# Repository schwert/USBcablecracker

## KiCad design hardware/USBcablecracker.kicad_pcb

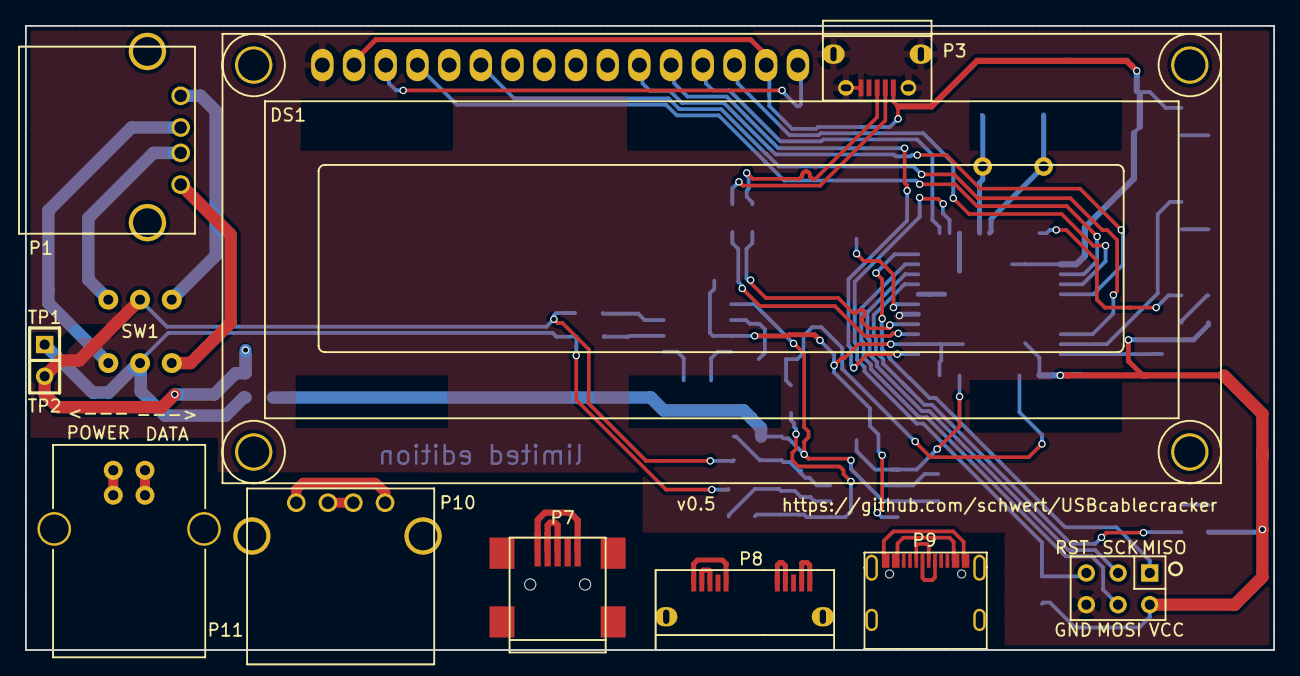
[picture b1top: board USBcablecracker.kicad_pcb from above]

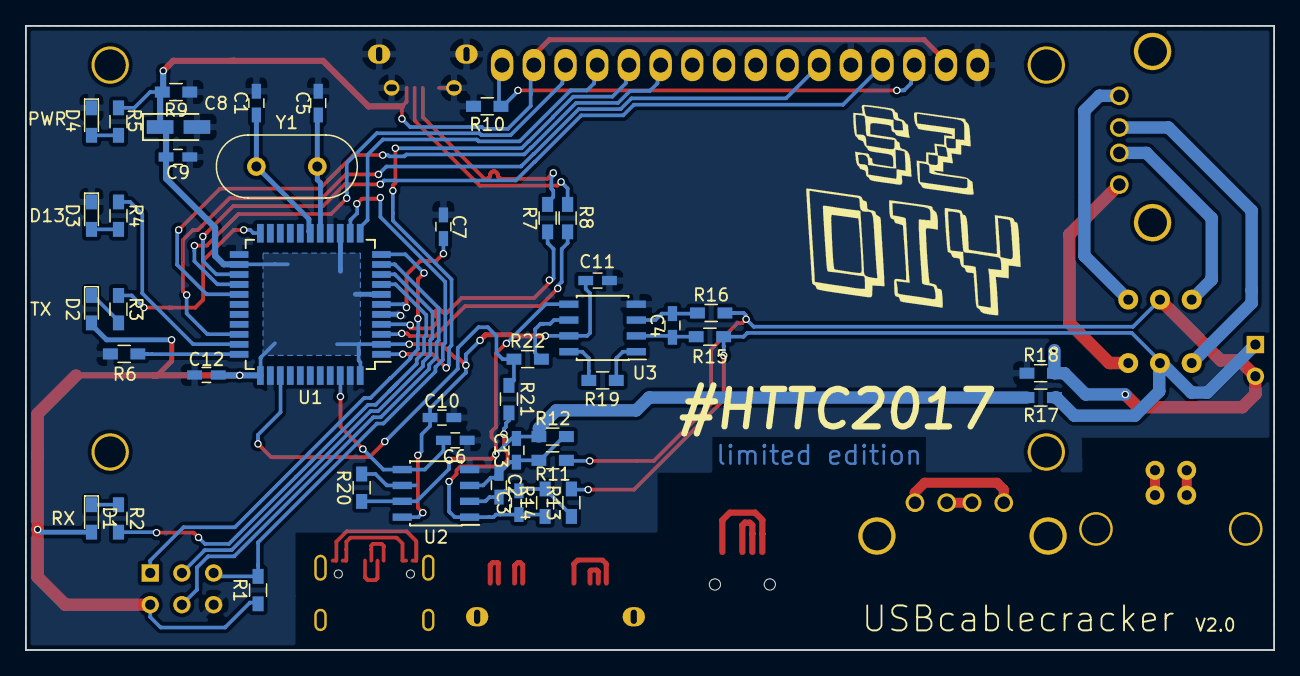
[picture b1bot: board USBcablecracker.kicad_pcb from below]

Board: 2 copper layers, 100.0 x 50.0 mm, 54 parts (43 on the bottom side), 60 nets.

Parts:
C1, C5: 15P; C_0603_HandSoldering
C2, C3, C4, C13: 1nF; C_0603_HandSoldering
C6, C9, C10, C11, C12: 100nF; C_0603_HandSoldering
C7: 1uF; C_0603_HandSoldering
C8: 22uF; Tantalum_Case-A_EIA-3216-18_Wave
CONN1: ICSP; CONN_2.54mm_2x3
D1: RX; LED_0603_HandSoldering
D2: TX; LED_0603_HandSoldering
D3: L; LED_0603_HandSoldering
D4: ON; LED_0603_HandSoldering
DS1: LCD16X2; WC1602A
P1, P10: USB_A
P2: CONN_01X02; CONN_2.54mm_1x2
P3: USB_B-Micro; USB_Micro-B
P7: USB_B-Mini; USB_Mini-B
P8: USB_B-Micro-3.0; USB_Micro-30
P9: USB_TYPEC-S; USBtypeC
P11: USB_B
R1, R9, R11, R13, R15, R16, R20, R21, R22: 10K; R_0603_HandSoldering
R2, R3, R4, R5, R6: 1K; R_0603_HandSoldering
R7, R8: 22R; R_0603_HandSoldering
R10: 91R; R_0603_HandSoldering
R12, R14: 100K; R_0603_HandSoldering
R17: 68; R_0603_HandSoldering
R18: 33; R_0603_HandSoldering
R19: 11k; R_0603_HandSoldering
SW1: Switch_SPDT_x2; pin_headers_switch
U1: ATmega32U4-AU; TQFP-44_10x10mm_Pitch0.8mm
U2: LMV358; SOIC-8_3.9x4.9mm_Pitch1.27mm
U3: AD623; SOIC-8_3.9x4.9mm_Pitch1.27mm
Y1: 16MHz; Crystal_HC49-U_Vertical

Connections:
+5V: C8.1, C9.2, C10.2, C11.2, C12.2, CONN1.2, D1.2, D2.2, DS1.2, DS1.15, P3.1, R1.1, R5.2, R9.2, U1.2, U1.7, U1.14, U1.24, U1.34, U1.44, U2.8, U3.7
/A0: R21.1, R22.1, U1.36
/AREF: C6.1, U1.42, U2.5
/D4: DS1.4, U1.25
/D5: DS1.6, U1.31
/D6: DS1.11, U1.27
/D7: DS1.12, U1.1
/D+: R7.1, U1.4
/D-: R8.1, U1.3
/DIN+: P3.3, R7.2
/DIN-: P3.2, R8.2
/HWB: R6.2, U1.33
/IO11: DS1.13, U1.12
/IO12: DS1.14, U1.26
/IO13: R4.2, U1.32
/MISO: CONN1.1, U1.11
/MOSI: CONN1.4, U1.10
/REFO: C13.2, R12.2, R17.1, R20.1, U2.7, U3.5
/RESET: CONN1.5, R1.2, U1.13
/RX_LED: R2.2, U1.8
/SCK: CONN1.3, U1.9
/TEST1: P9.A1, P9.A12, P9.B1, P9.B12
/TEST2: P9.A6, P9.B6
/TEST5: P9.A4, P9.A9, P9.B4, P9.B9
/TEST6: P9.A7, P9.B7
/TP1: P2.1, R13.2, R15.2, R17.2, SW1.2
/TP2: P2.2, R11.2, R16.2, R18.1, SW1.5
/TX_LED: R3.2, U1.22
/X+: C1.1, U1.17, Y1.1
/X-: C5.1, U1.16, Y1.2
GND: C1.2, C5.2, C6.2, C7.1, C8.2, C9.1, C10.1, C11.1, C12.1, CONN1.6, D3.1, D4.1, DS1.1, DS1.5, P3.5, P3.6, P3.7, P3.8, P3.9, R6.1, R9.1, R10.2, R18.2, U1.5, U1.15, U1.23, U1.35, U1.43, U2.4, U3.4
unnamed: C2.2, C3.2, R13.1, R14.2, U2.2
unnamed: C3.1, R14.1, R21.2, U2.1
unnamed: C4.1, R15.1, U3.2
unnamed: C4.2, R16.1, U3.3
unnamed: C7.2, U1.6
unnamed: C2.1, C13.1, R11.1, R12.1, U2.3
unnamed: D1.1, R2.1
unnamed: D2.1, R3.1
unnamed: D3.2, R4.1
unnamed: D4.2, R5.1
unnamed: DS1.3, DS1.16, R10.1
unnamed: P1.1, SW1.4
unnamed: P1.2, SW1.3
unnamed: P1.3, SW1.6
unnamed: P1.4, SW1.1
unnamed: P7.1, P7.5
unnamed: P7.2, P7.3
unnamed: P8.1, P8.5
unnamed: P8.2, P8.3
unnamed: P8.6, P8.7
unnamed: P8.9, P8.10
unnamed: P10.1, P10.4
unnamed: P10.2, P10.3
unnamed: P11.1, P11.4
unnamed: P11.2, P11.3
unnamed: R19.1, U3.8
unnamed: R19.2, U3.1
unnamed: R20.2, U2.6
unnamed: R22.2, U3.6

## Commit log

2017-11-05 Board cleanup first pass (still need to reconnect GND to U1)
2017-11-05 fixes net name (+5C to +5V), big hands -> big led pads
2017-11-08 no more GPIO breakout
2017-11-08 crystal placement
2017-11-08 fixes accidental deletion of U1
2017-11-08 proper repo URL
2017-11-08 silkscreen prettyness
2017-11-08 component designators placement
2017-11-08 missed a couple
2017-11-09 replacing switch by pin headers for easy sourcing
2017-11-23 reverted to original switch
